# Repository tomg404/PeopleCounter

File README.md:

# People sensor / door sensor project
I needed a sensor which detects if someone or something entered or left a room. as i didn't find anything online i decided
to hack together my own little sensor. 

In my first try I utilised two `hc-sr04` ultrasonic sensors, but i quickly realised that their accuracy is horrible.
Another problem was that using two sensors needs a huge timeout (30-60ms) between their distance measurements, otherwise
they  will interfere each other and the results are _unusable_. They work for applications where things move slow, but
for this project I needed more **speeeeed**.

So my second thought was that two light barriers would work best. But one light barrier needs two parts. A sender and a
receiver. So this is also not the best solution to my problem as I want to mount the sensor on a door frame and don't want 
cables running all over the door frame.

Then I learned about time-of-flight (tof) sensors. They measure the distance to an object by shooting an infrared light
ray against the object and wait until the light is reflected back into the receiver. So they can essentially act like
a light barrier. I bought two `vl53l0x` tof sensors for ~8eur, tested them and got to the conclusion that they are 
perfect for this application. Not only do they **not** interfere with each other when relatively close together, these
sensors can also be probed extremely fast. In the fastest mode (continuous back-to-back ranging mode) the sensor has a
measurement ready for use every 20ms. Additionally, I can take measurements from both sensors at the same time. This
adds up to 50 measurements per second, per sensor. This is plenty enough to track a person walking through a door.

# Sample schematic

# Case

# todo
- [ ] make project run from batteries
- [ ] use deep-sleep mode as tof sensors don't need to probe constantly (wakeup from small ir sensor?)
- [ ] wifi stuff

# Useful resources
* **esp8266**
  * exception decoder: https://www.dzombak.com/blog/2021/10/ESP8266-PlatformIO-Serial-Console-Monitoring-with-Exception-Decoding.html
  * exception codes/causes: https://www.espressif.com/sites/default/files/documentation/esp8266_reset_causes_and_common_fatal_exception_causes_en.pdf
  * pinout: https://cdn.shopify.com/s/files/1/1509/1638/files/D1_Mini_Pinout_Diagram.pdf?5603303439559815202
  * board versions: https://docs.wemos.cc/en/latest/d1/index.html

* **hc-sr04 ultrasonic sensor**
  * explanation of sensor: https://randomnerdtutorials.com/complete-guide-for-ultrasonic-sensor-hc-sr04/
  * data sheet: https://docs.google.com/document/d/1Y-yZnNhMYy7rwhAgyL_pfa39RsB-x2qR4vP8saG73rE/edit?pli=1
  * NewPing library: https://bitbucket.org/teckel12/arduino-new-ping/wiki
  * multiple ultrasonic sensors: https://bitbucket.org/teckel12/arduino-new-ping/wiki/Help%20with%2015%20Sensors%20Example%20Sketch

* **vl53l0x laser ranging sensor**
  * good explanation of sensor: https://wolles-elektronikkiste.de/vl53l0x-und-vl53l1x-tof-abstandssensoren
  * data sheet: https://www.st.com/resource/en/datasheet/vl53l0x.pdf

* **misc**
  * interrupts/timers: https://randomnerdtutorials.com/interrupts-timers-esp8266-arduino-ide-nodemcu/
  * finite state design pattern: https://www.aleksandrhovhannisyan.com/blog/implementing-a-finite-state-machine-in-cpp/#modeling-a-light-switch-in-code
  * fsm in c++: https://www.cppstories.com/2023/finite-state-machines-variant-cpp/

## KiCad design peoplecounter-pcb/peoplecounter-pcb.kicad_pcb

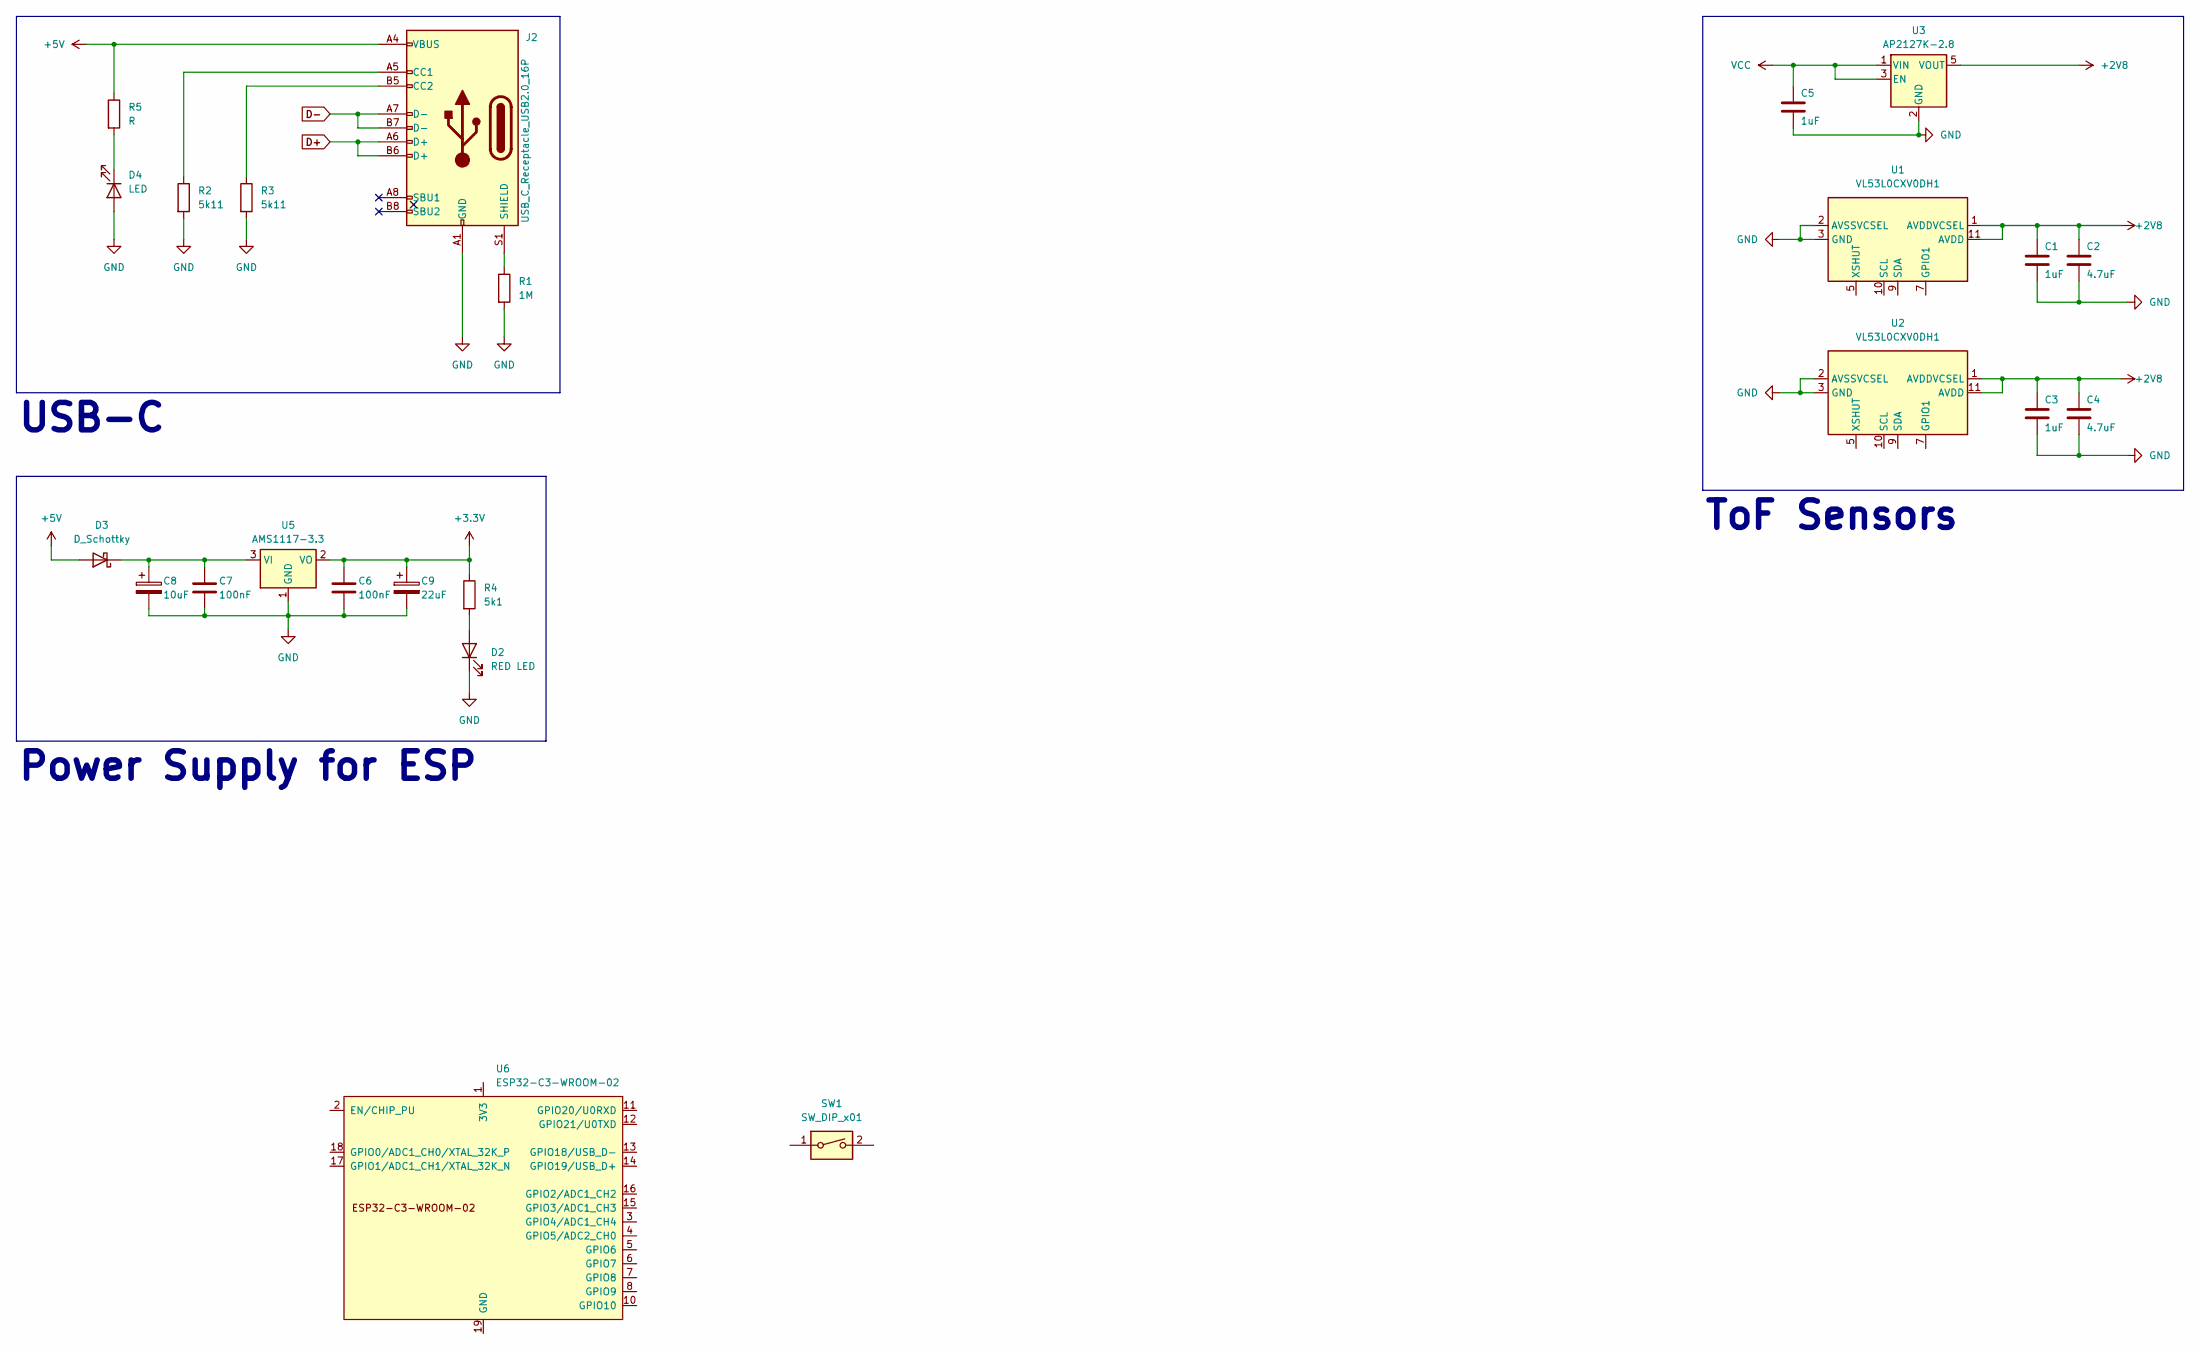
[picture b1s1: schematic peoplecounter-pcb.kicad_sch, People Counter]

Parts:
C1, C3, C5: 1uF; C_1206_3216Metric_Pad1.33x1.80mm_HandSolder
C2, C4: 4.7uF; C_1206_3216Metric_Pad1.33x1.80mm_HandSolder
C6, C7: 100nF; C_1206_3216Metric_Pad1.33x1.80mm_HandSolder
C8: 10uF; CP_Elec_5x5.3
C9: 22uF; CP_Elec_5x5.3
D2: RED LED; LED_1206_3216Metric_Pad1.42x1.75mm_HandSolder
D3: D_Schottky; D_1206_3216Metric_Pad1.42x1.75mm_HandSolder
D4: LED; LED_1206_3216Metric_Pad1.42x1.75mm_HandSolder
J2: USB_C_Receptacle_USB2.0_16P; USB_C_Receptacle_Amphenol_12401610E4-2A
R1: 1M; LED_1206_3216Metric_Pad1.42x1.75mm_HandSolder
R2, R3: 5k11; R_1206_3216Metric_Pad1.30x1.75mm_HandSolder
R4: 5k1; R_1206_3216Metric_Pad1.30x1.75mm_HandSolder
R5: R; R_1206_3216Metric_Pad1.30x1.75mm_HandSolder
SW1: SW_DIP_x01; SW_DIP_SPSTx01_Slide_Omron_A6S-110x_W8.9mm_P2.54mm
U1, U2: VL53L0CXV0DH1; ST_VL53L1x
U3: AP2127K-2.8; SOT-23-5
U5: AMS1117-3.3; SOT-223-3_TabPin2
U6: ESP32-C3-WROOM-02

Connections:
+2V8: C1.1, C2.1, C3.1, C4.1, U1.1 (AVDDVCSEL), U1.11 (AVDD), U2.1 (AVDDVCSEL), U2.11 (AVDD), U3.5 (VOUT)
+3.3V: C6.1, C9.1, R4.1, U5.2 (VO)
+5V: D3.2 (A), J2.A4 (VBUS), J2.A9 (VBUS), J2.B4 (VBUS), J2.B9 (VBUS), R5.1
D+: J2.A6 (D+), J2.B6 (D+)
D-: J2.A7 (D-), J2.B7 (D-)
GND: C1.2, C2.2, C3.2, C4.2, C5.2, C6.2, C7.2, C8.2, C9.2, D2.1 (K), D4.2 (A), J2.A1 (GND), J2.A12 (GND), J2.B1 (GND), J2.B12 (GND), R1.2, R2.2, R3.2, U1.2 (AVSSVCSEL), U1.3 (GND), U1.4 (GND), U1.6 (GND), U1.12 (GND), U2.2 (AVSSVCSEL), U2.3 (GND), U2.4 (GND), U2.6 (GND), U2.12 (GND), U3.2 (GND), U5.1 (GND)
unnamed: D2.2 (A), R4.2
unnamed: C7.1, C8.1, D3.1 (K), U5.3 (VI)
unnamed: D4.1 (K), R5.2
unnamed: J2.A5 (CC1), R2.1
unnamed: J2.B5 (CC2), R3.1
unnamed: J2.S1 (SHIELD), R1.1
unnamed: U6.9 (GND), U6.19 (GND)
VCC: C5.1, U3.1 (VIN), U3.3 (EN)

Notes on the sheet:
ToF Sensors
USB-C
Power Supply for ESP

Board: 2 copper layers, 25 parts (0 on the bottom side), 14 nets, no tracks yet.

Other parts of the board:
D1: LED_RBGA; LED_Kingbright_AAA3528ESGCT

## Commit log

2023-09-27 add readme
2023-09-27 add experimental LED class
2023-09-27 add clion config
2024-02-24 add kicad project files
